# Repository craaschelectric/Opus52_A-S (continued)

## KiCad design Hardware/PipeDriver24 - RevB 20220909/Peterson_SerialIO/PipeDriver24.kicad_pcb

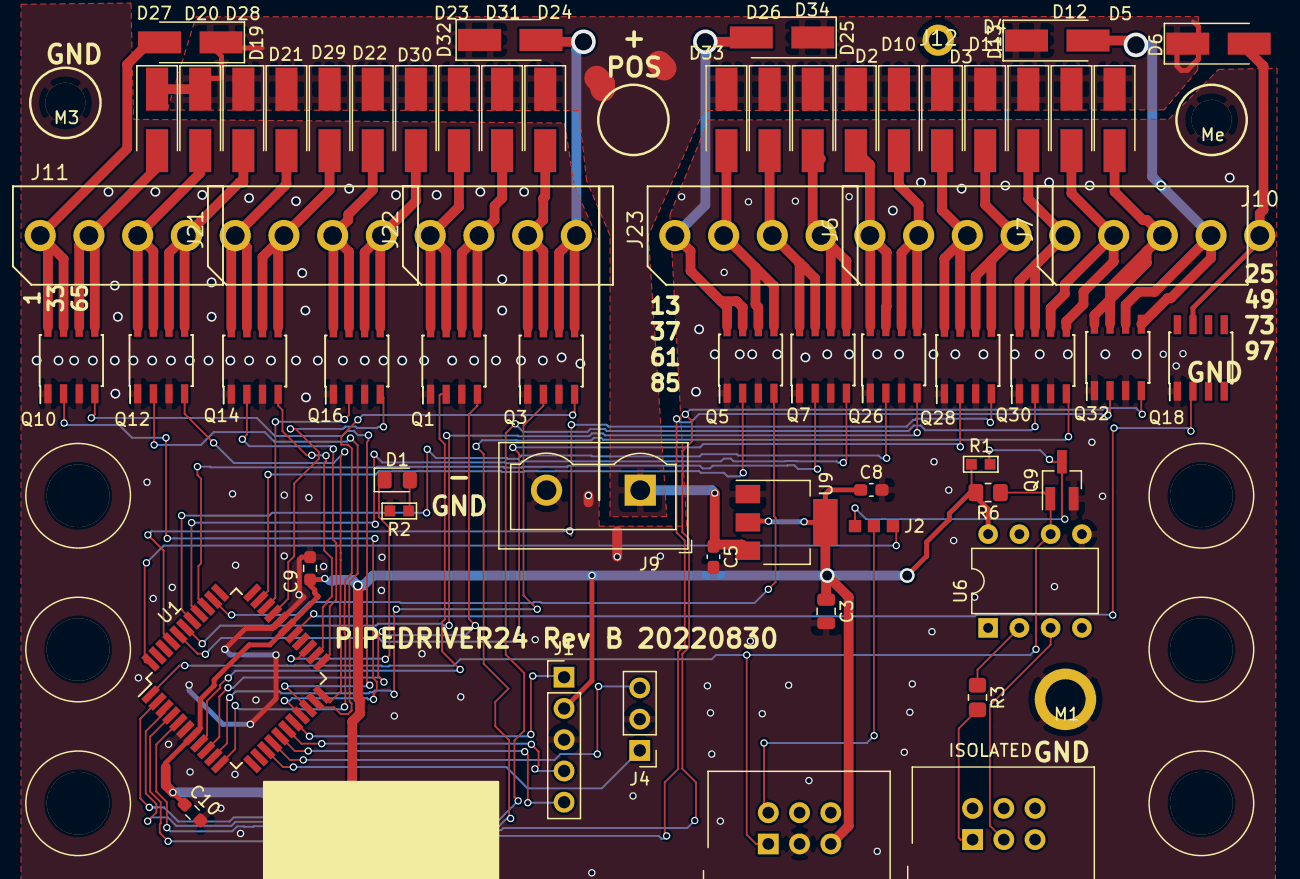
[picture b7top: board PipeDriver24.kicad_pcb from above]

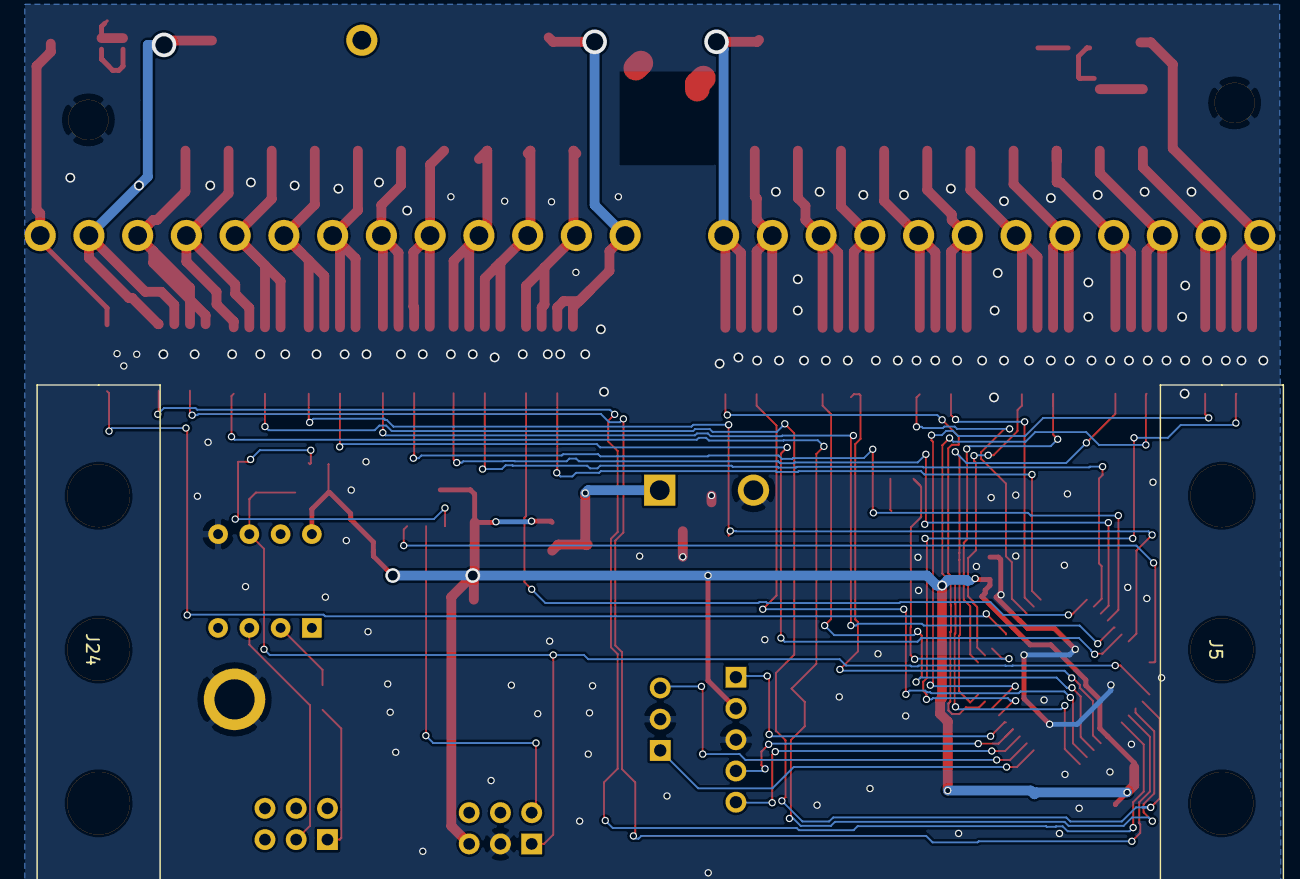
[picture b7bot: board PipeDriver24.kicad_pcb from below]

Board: 2 copper layers, 71 parts (2 on the bottom side), 67 nets.

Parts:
C3: 1u; C_0805_2012Metric
C5, C8: CERAMIC-100NF-50V-10%-X7R_0603_; C_0603_1608Metric_Pad1.08x0.95mm_HandSolder
C9: 1u; R_0603_1608Metric_Pad0.98x0.95mm_HandSolder
C10: 0.1u; R_0603_1608Metric_Pad0.98x0.95mm_HandSolder
D1: SMD-LED-CLEAR-GREEN_0805_; LED_0805_2012Metric_Pad1.15x1.40mm_HandSolder
D2, D3, D4, D5, D6, D10, D11, D12, D13, D19, D20, D21, D22, D23, D24, D25, D26, D27, D28, D29, D30, D31, D32, D33, D34: SK34; D_SMA_Handsoldering
J1: Conn_01x05; PinHeader_1x05_P2.54mm_Vertical
J2: Conn_01x03_Male; 0603Jumper
J3, J8: Conn_02x03_Odd_Even; RibbonCableSocket_6_OddEven
J4: Conn_01x03_Male; PinHeader_1x03_P2.54mm_Vertical
J5, J24: Conn_01x03-conn; Phoenix1202713 DIN Rail
J6, J7, J11, J21, J22, J23: Conn_01x04_Male; KK156-4
J9: Conn_01x02_Female; TerminalBlock_Wuerth_691311400102_P7.62mm
J10: Conn_01x01_Male; KK156-1
J12: Conn_01x01; KK156-1
M1, M3: Conn_01x01; Mounting#4
Me: Conn_01x01; Mounting#4
Q1, Q3, Q5, Q7, Q10, Q12, Q14, Q16, Q18, Q26, Q28, Q30, Q32: SI4288; SOIC-8_3.9x4.9mm_P1.27mm
Q9: AO3404; SOT-23_Handsoldering
R1: 220; R0603
R2: DNP; R0603
R3, R6: 220; R_0805_2012Metric_Pad1.20x1.40mm_HandSolder
U1: PIC16F15375-IPT; LQFP-44_10x10mm_P0.8mm
U6: 6N138; DIP-8_W7.62mm
U9: AP1117-33; SOT-223-3_TabPin2

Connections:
/DRVA00: Q10.2, U1.19
/DRVA01: Q10.4, U1.20
/DRVA02: Q12.2, U1.21
/DRVA03: Q12.4, U1.22
/DRVA04: Q14.2, U1.23
/DRVA05: Q14.4, U1.24
/DRVA06: Q16.2, U1.31
/DRVA07: Q16.4, U1.30
/DRVA08: Q1.2, U1.8
/DRVA09: Q1.4, U1.9
/DRVA10: Q3.2, U1.10
/DRVA11: Q3.4, U1.11
/DRVA12: Q5.2, U1.32
/DRVA13: Q5.4, U1.35
/DRVA14: Q7.2, U1.36
/DRVA15: Q7.4, U1.37
/DRVB00: Q26.2, U1.38
/DRVB01: Q26.4, U1.39
/DRVB02: Q28.2, U1.40
/DRVB03: Q28.4, U1.41
/DRVB04: Q30.2, U1.2
/DRVB05: Q30.4, U1.3
/DRVB06: Q32.2, U1.4
/DRVB07: Q32.4, U1.5
/DRVB08: Q18.2, U1.27
/ICLK: J1.5, U1.16
/IDTA: J1.4, U1.17
/LEDDRV: D1.1, U1.25
/SAMA00: D19.1, J11.1, Q10.7, Q10.8
/SAMA01: D27.1, J11.2, Q10.5, Q10.6
/SAMA02: D20.1, J11.3, Q12.7, Q12.8
/SAMA03: D28.1, J11.4, Q12.5, Q12.6
/SAMA04: D21.1, J21.1, Q14.7, Q14.8
/SAMA05: D29.1, J21.2, Q14.5, Q14.6
/SAMA06: D22.1, J21.3, Q16.7, Q16.8
/SAMA07: D30.1, J21.4, Q16.5, Q16.6
/SAMA08: D23.1, J22.1, Q1.7, Q1.8
/SAMA09: D31.1, J22.2, Q1.5, Q1.6
/SAMA10: D24.1, J22.3, Q3.7, Q3.8
/SAMA11: D32.1, J22.4, Q3.5, Q3.6
/SAMA12: D25.1, J23.1, Q5.7, Q5.8
/SAMA13: D33.1, J23.2, Q5.5, Q5.6
/SAMA14: D26.1, J23.3, Q7.7, Q7.8
/SAMA15: D34.1, J23.4, Q7.5, Q7.6
/SAMB00: D2.1, J6.1, Q26.7, Q26.8
/SAMB01: D10.1, J6.2, Q26.5, Q26.6
/SAMB02: D3.1, J6.3, Q28.7, Q28.8
/SAMB03: D11.1, J6.4, Q28.5, Q28.6
/SAMB04: D4.1, J7.1, Q30.7, Q30.8
/SAMB05: D12.1, J7.2, Q30.5, Q30.6
/SAMB06: D5.1, J7.3, Q32.7, Q32.8
/SAMB07: D13.1, J7.4, Q32.5, Q32.6
/SAMB08: D6.1, J10.1, Q18.7, Q18.8
/nMCLR: J1.1, U1.18
GND: C3.2, C5.2, C8.2, C9.2, C10.2, J1.3, J4.2, J8.3, J9.2, M1.1, M3.1, Me.1, Q1.1, Q1.3, Q3.1, Q3.3, Q5.1, Q5.3, Q7.1, Q7.3, Q9.2, Q10.1, Q10.3, Q12.1, Q12.3, Q14.1, Q14.3, Q16.1, Q16.3, Q18.1, Q26.1, Q26.3, Q28.1, Q28.3, Q30.1, Q30.3, Q32.1, Q32.3, R2.2, U1.6, U1.29, U6.5, U9.1
unnamed: D1.2, R2.1
unnamed: J2.1, U1.44
unnamed: J2.3, Q9.3, R1.2
unnamed: J3.1, R3.2
unnamed: J3.3, U6.3
unnamed: J4.1, U1.14
unnamed: J4.3, U1.15
unnamed: R3.1, U6.2
SAMPWR: C5.1, D2.2, D3.2, D4.2, D5.2, D6.2, D10.2, D11.2, D12.2, D13.2, D19.2, D20.2, D21.2, D22.2, D23.2, D24.2, D25.2, D26.2, D27.2, D28.2, D29.2, D30.2, D31.2, D32.2, D33.2, D34.2, J9.1, J12.1, U9.3
SERDRV: J2.2, J8.2
SERIN: J8.1, Q9.1, R6.1, U1.1, U6.6
VCC: C3.1, C8.1, C9.1, C10.1, J1.2, J8.5, R1.1, R6.2, U1.7, U1.28, U6.8, U9.2

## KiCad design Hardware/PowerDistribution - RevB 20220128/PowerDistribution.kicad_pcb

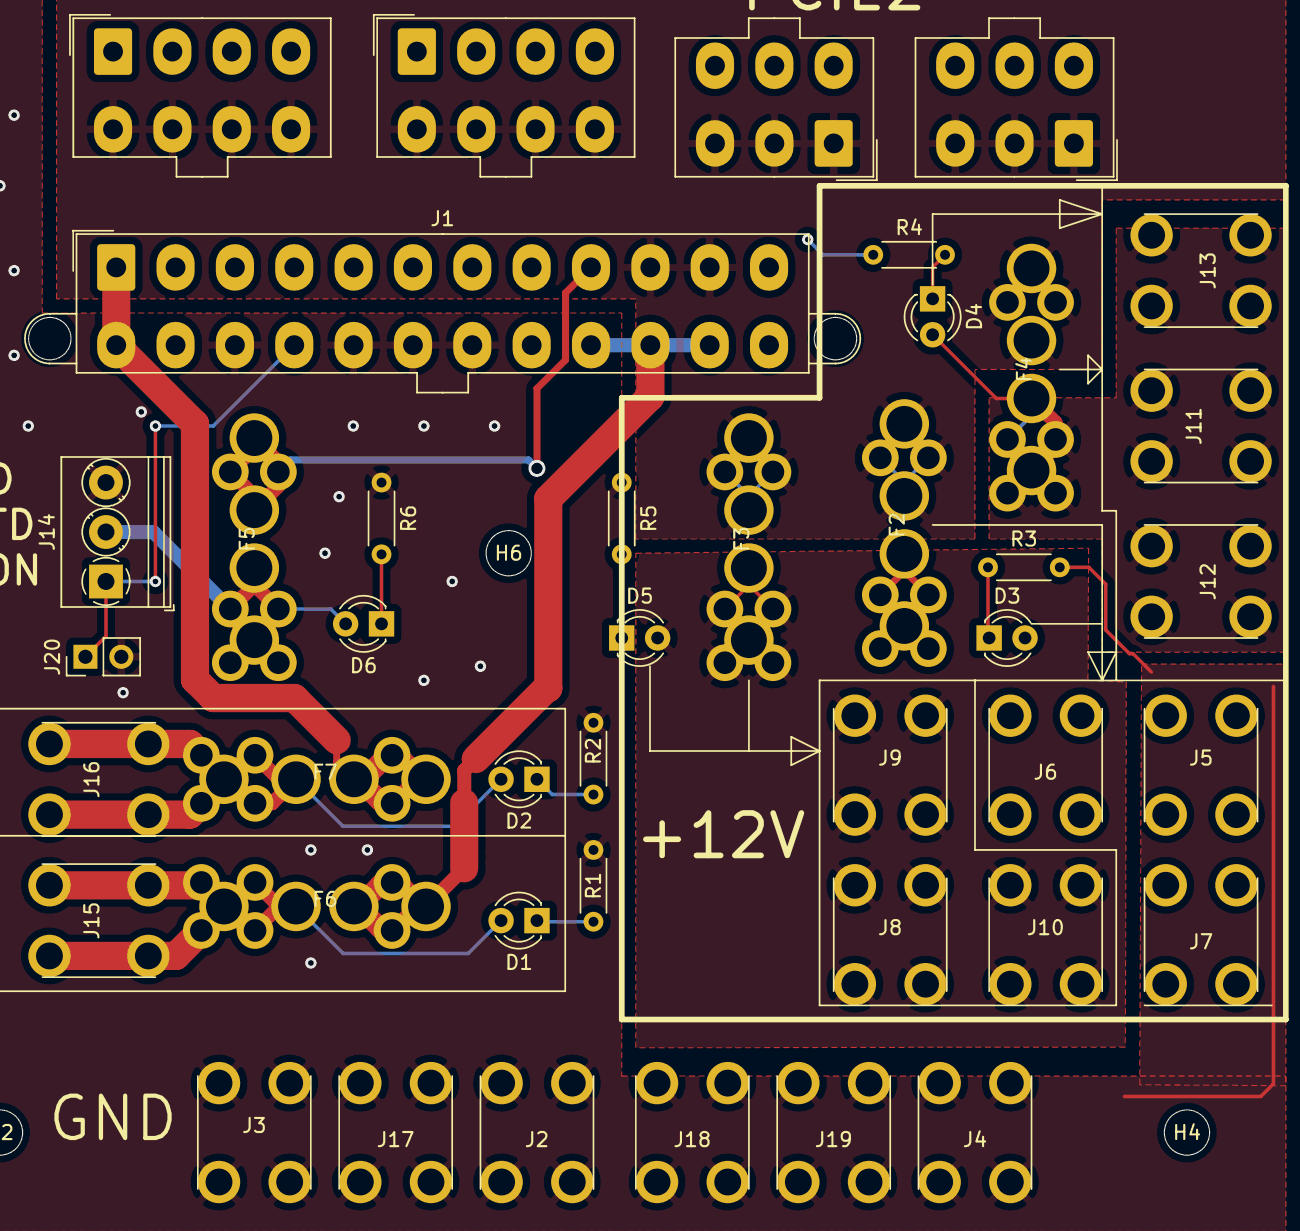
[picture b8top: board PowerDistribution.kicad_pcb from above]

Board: 2 copper layers, 48 parts (0 on the bottom side), 18 nets.

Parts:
D1, D2, D3, D4, D5, D6: LED; LED_D3.0mm
EPS1, EPS2: Conn_02x04_Top_Bottom; Molex_Mini-Fit_Jr_5566-08A_2x04_P4.20mm_Vertical
F2, F3, F4, F5, F6, F7: Keystone 3522x2 or 3557x2; Keystone 3522x2 fuse
H1, H2, H3, H4, H5, H6: MountingHole; MountingHole_3.2mm_M3
J1: Molex MiniFit JR 5566 4.2mm; Molex_Mini-Fit_Jr_5566-24A2_2x12_P4.20mm_Vertical
J2, J3, J4, J5, J6, J7, J8, J9, J10, J11, J12, J13, J15, J16, J17, J18, J19: Keystone 8191; Keystone 8191 Screw Term
J14: Phoenix 1984772; TerminalBlock_Phoenix_PT-1,5-3-3.5-H_1x03_P3.50mm_Horizontal
J20: Conn_02x01; PinHeader_1x02_P2.54mm_Vertical
PCIE1, PCIE2: Molex 5566; Molex_Mini-Fit_Jr_5566-06A_2x03_P4.20mm_Vertical
R1, R2, R3, R4, R5, R6: R; R_Axial_DIN0204_L3.6mm_D1.6mm_P5.08mm_Horizontal

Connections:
+3V3: F7.1, J1.1, J1.13
+5V: F6.1, J1.21, J1.22, J1.23
+12V: EPS1.5, EPS1.6, EPS1.7, EPS1.8, EPS2.5, EPS2.6, EPS2.7, EPS2.8, F2.1, F3.1, F4.1, J1.10, J1.11, PCIE1.1, PCIE1.2, PCIE1.3, PCIE2.1, PCIE2.2, PCIE2.3
/5BSTDBY: F5.1, J1.9
/nPSON: J1.16, J14.1, J20.1
GND: EPS1.1, EPS1.2, EPS1.3, EPS1.4, EPS2.1, EPS2.2, EPS2.3, EPS2.4, J1.3, J1.5, J1.7, J1.15, J1.17, J1.18, J1.19, J1.24, J2.1, J3.1, J4.1, J14.3, J17.1, J18.1, J19.1, J20.2, PCIE1.4, PCIE1.5, PCIE1.6, PCIE2.4, PCIE2.5, PCIE2.6, R1.1, R2.1, R3.1, R4.1, R5.1, R6.1
unnamed: D1.1, R1.2
unnamed: D1.2, F6.2, J15.1
unnamed: D2.1, R2.2
unnamed: D2.2, F7.2, J16.1
unnamed: D3.1, R3.2
unnamed: D3.2, F2.2, J5.1, J6.1, J7.1
unnamed: D4.1, R4.2
unnamed: D4.2, F4.2, J11.1, J12.1, J13.1
unnamed: D5.1, R5.2
unnamed: D5.2, F3.2, J8.1, J9.1, J10.1
unnamed: D6.1, R6.2
unnamed: D6.2, F5.2, J14.2

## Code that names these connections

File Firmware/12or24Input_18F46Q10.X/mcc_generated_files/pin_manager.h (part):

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// get/set D0 aliases
#define D0_TRIS                 TRISAbits.TRISA0
#define D0_LAT                  LATAbits.LATA0
#define D0_PORT                 PORTAbits.RA0
#define D0_WPU                  WPUAbits.WPUA0
#define D0_OD                   ODCONAbits.ODCA0
#define D0_ANS                  ANSELAbits.ANSELA0
#define D0_SetHigh()            do { LATAbits.LATA0 = 1; } while(0)
#define D0_SetLow()             do { LATAbits.LATA0 = 0; } while(0)
#define D0_Toggle()             do { LATAbits.LATA0 = ~LATAbits.LATA0; } while(0)
#define D0_GetValue()           PORTAbits.RA0
#define D0_SetDigitalInput()    do { TRISAbits.TRISA0 = 1; } while(0)
#define D0_SetDigitalOutput()   do { TRISAbits.TRISA0 = 0; } while(0)
#define D0_SetPullup()          do { WPUAbits.WPUA0 = 1; } while(0)
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// get/set D1 aliases
#define D1_TRIS                 TRISAbits.TRISA1
#define D1_LAT                  LATAbits.LATA1
#define D1_PORT                 PORTAbits.RA1
#define D1_WPU                  WPUAbits.WPUA1
#define D1_OD                   ODCONAbits.ODCA1
#define D1_ANS                  ANSELAbits.ANSELA1
#define D1_SetHigh()            do { LATAbits.LATA1 = 1; } while(0)
#define D1_SetLow()             do { LATAbits.LATA1 = 0; } while(0)
#define D1_Toggle()             do { LATAbits.LATA1 = ~LATAbits.LATA1; } while(0)
#define D1_GetValue()           PORTAbits.RA1
#define D1_SetDigitalInput()    do { TRISAbits.TRISA1 = 1; } while(0)
#define D1_SetDigitalOutput()   do { TRISAbits.TRISA1 = 0; } while(0)
#define D1_SetPullup()          do { WPUAbits.WPUA1 = 1; } while(0)
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// get/set D2 aliases
#define D2_TRIS                 TRISAbits.TRISA2
#define D2_LAT                  LATAbits.LATA2
#define D2_PORT                 PORTAbits.RA2
#define D2_WPU                  WPUAbits.WPUA2
#define D2_OD                   ODCONAbits.ODCA2
#define D2_ANS                  ANSELAbits.ANSELA2
#define D2_SetHigh()            do { LATAbits.LATA2 = 1; } while(0)
#define D2_SetLow()             do { LATAbits.LATA2 = 0; } while(0)
#define D2_Toggle()             do { LATAbits.LATA2 = ~LATAbits.LATA2; } while(0)
#define D2_GetValue()           PORTAbits.RA2
#define D2_SetDigitalInput()    do { TRISAbits.TRISA2 = 1; } while(0)
#define D2_SetDigitalOutput()   do { TRISAbits.TRISA2 = 0; } while(0)
#define D2_SetPullup()          do { WPUAbits.WPUA2 = 1; } while(0)
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// get/set D3 aliases
#define D3_TRIS                 TRISAbits.TRISA3
#define D3_LAT                  LATAbits.LATA3
#define D3_PORT                 PORTAbits.RA3
#define D3_WPU                  WPUAbits.WPUA3
#define D3_OD                   ODCONAbits.ODCA3
#define D3_ANS                  ANSELAbits.ANSELA3
#define D3_SetHigh()            do { LATAbits.LATA3 = 1; } while(0)
#define D3_SetLow()             do { LATAbits.LATA3 = 0; } while(0)
#define D3_Toggle()             do { LATAbits.LATA3 = ~LATAbits.LATA3; } while(0)
#define D3_GetValue()           PORTAbits.RA3
#define D3_SetDigitalInput()    do { TRISAbits.TRISA3 = 1; } while(0)
#define D3_SetDigitalOutput()   do { TRISAbits.TRISA3 = 0; } while(0)
#define D3_SetPullup()          do { WPUAbits.WPUA3 = 1; } while(0)
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// get/set D4 aliases
#define D4_TRIS                 TRISAbits.TRISA4
#define D4_LAT                  LATAbits.LATA4
#define D4_PORT                 PORTAbits.RA4
#define D4_WPU                  WPUAbits.WPUA4
#define D4_OD                   ODCONAbits.ODCA4
#define D4_ANS                  ANSELAbits.ANSELA4
#define D4_SetHigh()            do { LATAbits.LATA4 = 1; } while(0)
#define D4_SetLow()             do { LATAbits.LATA4 = 0; } while(0)
#define D4_Toggle()             do { LATAbits.LATA4 = ~LATAbits.LATA4; } while(0)
#define D4_GetValue()           PORTAbits.RA4
#define D4_SetDigitalInput()    do { TRISAbits.TRISA4 = 1; } while(0)
#define D4_SetDigitalOutput()   do { TRISAbits.TRISA4 = 0; } while(0)
#define D4_SetPullup()          do { WPUAbits.WPUA4 = 1; } while(0)
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// get/set D5 aliases
#define D5_TRIS                 TRISAbits.TRISA5
#define D5_LAT                  LATAbits.LATA5
#define D5_PORT                 PORTAbits.RA5
#define D5_WPU                  WPUAbits.WPUA5
#define D5_OD                   ODCONAbits.ODCA5
#define D5_ANS                  ANSELAbits.ANSELA5
#define D5_SetHigh()            do { LATAbits.LATA5 = 1; } while(0)
#define D5_SetLow()             do { LATAbits.LATA5 = 0; } while(0)
#define D5_Toggle()             do { LATAbits.LATA5 = ~LATAbits.LATA5; } while(0)
#define D5_GetValue()           PORTAbits.RA5
#define D5_SetDigitalInput()    do { TRISAbits.TRISA5 = 1; } while(0)
#define D5_SetDigitalOutput()   do { TRISAbits.TRISA5 = 0; } while(0)
#define D5_SetPullup()          do { WPUAbits.WPUA5 = 1; } while(0)
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// get/set D6 aliases
#define D6_TRIS                 TRISAbits.TRISA6
#define D6_LAT                  LATAbits.LATA6
#define D6_PORT                 PORTAbits.RA6
#define D6_WPU                  WPUAbits.WPUA6
#define D6_OD                   ODCONAbits.ODCA6
#define D6_ANS                  ANSELAbits.ANSELA6
#define D6_SetHigh()            do { LATAbits.LATA6 = 1; } while(0)
#define D6_SetLow()             do { LATAbits.LATA6 = 0; } while(0)
#define D6_Toggle()             do { LATAbits.LATA6 = ~LATAbits.LATA6; } while(0)
#define D6_GetValue()           PORTAbits.RA6
#define D6_SetDigitalInput()    do { TRISAbits.TRISA6 = 1; } while(0)
#define D6_SetDigitalOutput()   do { TRISAbits.TRISA6 = 0; } while(0)
#define D6_SetPullup()          do { WPUAbits.WPUA6 = 1; } while(0)
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// get/set D7 aliases
#define D7_TRIS                 TRISAbits.TRISA7
#define D7_LAT                  LATAbits.LATA7
#define D7_PORT                 PORTAbits.RA7
#define D7_WPU                  WPUAbits.WPUA7
#define D7_OD                   ODCONAbits.ODCA7
#define D7_ANS                  ANSELAbits.ANSELA7
#define D7_SetHigh()            do { LATAbits.LATA7 = 1; } while(0)
#define D7_SetLow()             do { LATAbits.LATA7 = 0; } while(0)
#define D7_Toggle()             do { LATAbits.LATA7 = ~LATAbits.LATA7; } while(0)
#define D7_GetValue()           PORTAbits.RA7
#define D7_SetDigitalInput()    do { TRISAbits.TRISA7 = 1; } while(0)
#define D7_SetDigitalOutput()   do { TRISAbits.TRISA7 = 0; } while(0)
#define D7_SetPullup()          do { WPUAbits.WPUA7 = 1; } while(0)
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// get/set SYNC aliases
#define SYNC_TRIS                 TRISBbits.TRISB2
#define SYNC_LAT                  LATBbits.LATB2
#define SYNC_PORT                 PORTBbits.RB2
#define SYNC_WPU                  WPUBbits.WPUB2
#define SYNC_OD                   ODCONBbits.ODCB2
#define SYNC_ANS                  ANSELBbits.ANSELB2
#define SYNC_SetHigh()            do { LATBbits.LATB2 = 1; } while(0)
#define SYNC_SetLow()             do { LATBbits.LATB2 = 0; } while(0)
#define SYNC_Toggle()             do { LATBbits.LATB2 = ~LATBbits.LATB2; } while(0)
#define SYNC_GetValue()           PORTBbits.RB2
#define SYNC_SetDigitalInput()    do { TRISBbits.TRISB2 = 1; } while(0)
#define SYNC_SetDigitalOutput()   do { TRISBbits.TRISB2 = 0; } while(0)
#define SYNC_SetPullup()          do { WPUBbits.WPUB2 = 1; } while(0)
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// get/set MSTOUT aliases
#define MSTOUT_TRIS                 TRISBbits.TRISB3
#define MSTOUT_LAT                  LATBbits.LATB3
#define MSTOUT_PORT                 PORTBbits.RB3
#define MSTOUT_WPU                  WPUBbits.WPUB3
#define MSTOUT_OD                   ODCONBbits.ODCB3
#define MSTOUT_ANS                  ANSELBbits.ANSELB3
#define MSTOUT_SetHigh()            do { LATBbits.LATB3 = 1; } while(0)
#define MSTOUT_SetLow()             do { LATBbits.LATB3 = 0; } while(0)
#define MSTOUT_Toggle()             do { LATBbits.LATB3 = ~LATBbits.LATB3; } while(0)
#define MSTOUT_GetValue()           PORTBbits.RB3
#define MSTOUT_SetDigitalInput()    do { TRISBbits.TRISB3 = 1; } while(0)
#define MSTOUT_SetDigitalOutput()   do { TRISBbits.TRISB3 = 0; } while(0)
#define MSTOUT_SetPullup()          do { WPUBbits.WPUB3 = 1; } while(0)
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// get/set PEROUT aliases
#define PEROUT_TRIS                 TRISBbits.TRISB4
#define PEROUT_LAT                  LATBbits.LATB4
#define PEROUT_PORT                 PORTBbits.RB4
#define PEROUT_WPU                  WPUBbits.WPUB4
#define PEROUT_OD                   ODCONBbits.ODCB4
#define PEROUT_ANS                  ANSELBbits.ANSELB4
#define PEROUT_SetHigh()            do { LATBbits.LATB4 = 1; } while(0)
#define PEROUT_SetLow()             do { LATBbits.LATB4 = 0; } while(0)
#define PEROUT_Toggle()             do { LATBbits.LATB4 = ~LATBbits.LATB4; } while(0)
#define PEROUT_GetValue()           PORTBbits.RB4
#define PEROUT_SetDigitalInput()    do { TRISBbits.TRISB4 = 1; } while(0)
#define PEROUT_SetDigitalOutput()   do { TRISBbits.TRISB4 = 0; } while(0)
#define PEROUT_SetPullup()          do { WPUBbits.WPUB4 = 1; } while(0)
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// get/set CLK aliases
#define CLK_TRIS                 TRISBbits.TRISB5
#define CLK_LAT                  LATBbits.LATB5
#define CLK_PORT                 PORTBbits.RB5
#define CLK_WPU                  WPUBbits.WPUB5
#define CLK_OD                   ODCONBbits.ODCB5
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
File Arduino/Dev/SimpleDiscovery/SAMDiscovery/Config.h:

// Config.h
// SAM Discovery Tool - Hardcoded Configuration

#ifndef CONFIG_H
#define CONFIG_H

#include <Arduino.h>

// ============================================================
// Chain Configuration
// ============================================================

// Number of chains actually in use
constexpr uint8_t NUMBER_OF_CHAINS = 2;
// Maximum chains supported
constexpr uint8_t MAX_CHAINS = 8;

// Chain types
constexpr uint8_t CHAIN_TYPE_597 = 0;       // 74HC596/597 chains
constexpr uint8_t CHAIN_TYPE_MULTIDROP = 1; // Multidrop SAM bus

// Chain Pin Configuration (order: in/out/sync/clock)
// Pins for chains 2-7 are placeholders (255 = unused)
//                                     Chain:    0     1     2     3     4     5     6     7
constexpr uint8_t CHAIN_DATA_IN_PIN[]        = {   35,    23,  255,  255,  255,  255,  255,  255 };
constexpr uint8_t CHAIN_DATA_OUT_PIN[]       = {   14,    22,  255,  255,  255,  255,  255,  255 };
constexpr uint8_t CHAIN_SYNC_PIN[]           = {   34,   21,  255,  255,  255,  255,  255,  255 };
constexpr uint8_t CHAIN_CLOCK_PIN[]          = {   33,   0,  255,  255,  255,  255,  255,  255 };
constexpr uint8_t CHAIN_TYPE[]               = {   0,    0,    0,    0,    0,    0,    0,    0 }; // 0=597, 1=MULTIDROP

// ============================================================
// SAM Discovery Configuration (hardcoded)
// ============================================================

// Stop sense inputs
constexpr uint8_t SENSE_CHAIN = 0;
constexpr uint8_t SENSE_CHAIN_TYPE = CHAIN_TYPE_597;
constexpr uint16_t SENSE_START_BIT = 0;
constexpr uint16_t SENSE_END_BIT = 127;

// Stop coil outputs
constexpr uint8_t COIL_CHAIN = 1;
constexpr uint8_t COIL_CHAIN_TYPE = CHAIN_TYPE_597;
constexpr uint16_t COIL_START_BIT = 0;
constexpr uint16_t COIL_END_BIT = 127;

// ============================================================
// Timing Constants
// ============================================================

constexpr uint32_t BIT_TIME_US = 10;
constexpr uint32_t SYNC_HIGH_US = 10;
constexpr uint32_t SYNC_HOLD_US = 10;
constexpr uint32_t SAM_PULSE_MS = 200;
constexpr uint32_t SAM_SETTLE_MS = 250;

// ============================================================
// Display Pins (ILI9341 320x240)
// ============================================================

constexpr uint8_t TFT_CS = 10;
constexpr uint8_t TFT_DC = 9;
constexpr uint8_t TOUCH_CS = 8;

// ============================================================
// Power Supply
// ============================================================

constexpr uint8_t POWER_ENABLE_PIN = 17;
constexpr uint8_t PERIPH_ENABLE_PIN = 1;

// ============================================================
// System Limits
// ============================================================

constexpr uint8_t MAX_STOPS = 255;
constexpr uint8_t WORDS_PER_CHAIN = 16;  // 16 words x 16 bits = 256 bits per chain
constexpr uint16_t MAX_BITS_PER_CHAIN = 256;

// Disabled address marker
constexpr uint16_t ADDR_DISABLED = 0x800;

#endif // CONFIG_H

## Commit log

2026-02-26 Initial commit: Initial Completed release of Opus 52 conversion. Designed for Grand Orgue, but Hauptwerk can be used
2026-03-11 Shoe mechanicals, Arduino updates
2026-03-15 SET and MEM+ collision
